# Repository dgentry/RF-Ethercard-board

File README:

This is an ENC28J60 breakout board created by maniacbug.

http://maniacbug.wordpress.com/2011/07/10/arduino-ethernet-using-enc28j60/

The latest checkin is a new layout for the board.

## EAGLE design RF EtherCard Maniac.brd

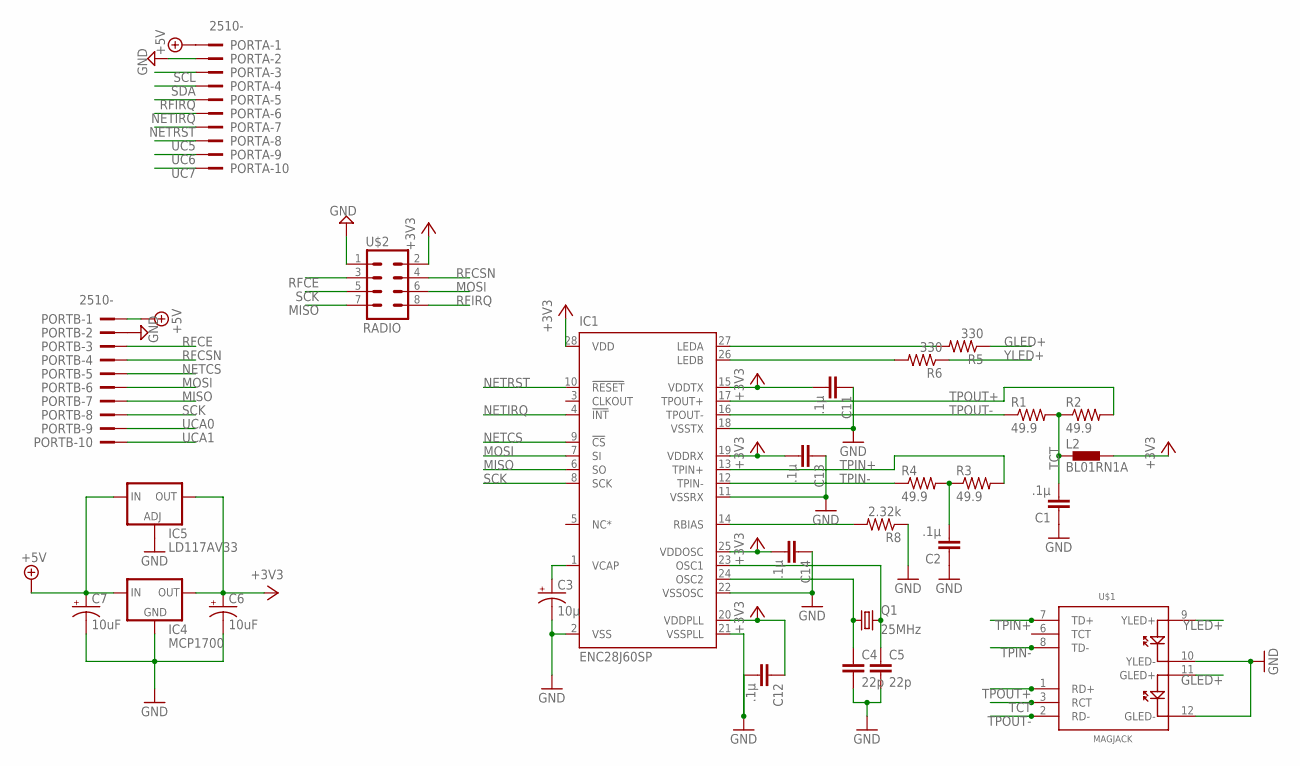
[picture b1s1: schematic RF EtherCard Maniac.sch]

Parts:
C1, C2, C11, C12, C13, C14: .1µ; CAP-PTH-SMALL
C3: 10µ; CPOL-RADIAL-10UF-25V
C4, C5: 22p; CAP-PTH-SMALL
C6, C7: 10uF; CPOL-RADIAL-10UF-25V
IC1: ENC28J60SP; DIL28-3
IC4: MCP1700; TO92A
IC5: LD117AV33; TO220L1
L2: BL01RN1A
PORTA: 2510-; PAK100/2500-10
PORTB: 2510-; PAK100/2500-10
Q1: 25MHz; HC49US
R1, R2, R3, R4: 49.9; AXIAL-0.3
R5, R6: 330; AXIAL-0.3
R8: 2.32k; AXIAL-0.3
U$1: MAGJACK
U$2: RADIO; 2X4

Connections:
+3V3: C6.1 (+), C11.2, C12.1, C13.2, C14.2, IC1.15 (VDDTX), IC1.19 (VDDRX), IC1.20 (VDDPLL), IC1.25 (VDDOSC), IC1.28 (VDD), IC4.3 (OUT), IC5.2 (OUT), L2.2, U$2.2
+5V: C7.1 (+), IC4.2 (IN), IC5.3 (IN), PORTA.1, PORTB.1
GLED+: R5.P$1 (1), U$1.11 (GLED+)
GND: C1.1, C2.1, C3.2 (-), C4.2, C5.2, C6.2 (-), C7.2 (-), C11.1, C12.2, C13.1, C14.1, IC1.2 (VSS), IC1.11 (VSSRX), IC1.18 (VSSTX), IC1.21 (VSSPLL), IC1.22 (VSSOSC), IC4.1 (GND), IC5.1 (ADJ), PORTA.2, PORTB.2, R8.P$1 (1), U$1.10 (YLED-), U$1.12 (GLED-), U$2.1
LEDA: IC1.27 (LEDA), R5.P$2 (2)
LEDB: IC1.26 (LEDB), R6.P$2 (2)
MISO: IC1.6 (SO), PORTB.7, U$2.7
MOSI: IC1.7 (SI), PORTB.6, U$2.6
unnamed: IC1.14 (RBIAS), R8.P$2 (2)
unnamed: C4.1, IC1.24 (OSC2), Q1.1
unnamed: C5.1, IC1.23 (OSC1), Q1.2
NETCS: IC1.9 (!CS), PORTB.5
NETIRQ: IC1.4 (!INT), PORTA.6
NETRST: IC1.10 (!RESET), PORTA.7
RFCE: PORTB.3, U$2.3
RFCSN: PORTB.4, U$2.4
RFIRQ: PORTA.5, U$2.8
SCK: IC1.8 (SCK), PORTB.8, U$2.5
SCL: PORTA.3
SDA: PORTA.4
TCT: C1.2, L2.1, R1.P$2 (2), R2.P$1 (1), U$1.3 (RCT)
TPGND: C2.2, R3.P$1 (1), R4.P$2 (2)
TPIN+: IC1.13 (TPIN+), R3.P$2 (2), U$1.7 (TD+)
TPIN-: IC1.12 (TPIN-), R4.P$1 (1), U$1.8 (TD-)
TPOUT+: IC1.17 (TPOUT+), R2.P$2 (2), U$1.1 (RD+)
TPOUT-: IC1.16 (TPOUT-), R1.P$1 (1), U$1.2 (RD-)
UC5: PORTA.8
UC6: PORTA.9
UC7: PORTA.10
UCA0: PORTB.9
UCA1: PORTB.10
VCAP: C3.1 (+), IC1.1 (VCAP)
YLED+: R6.P$1 (1), U$1.9 (YLED+)

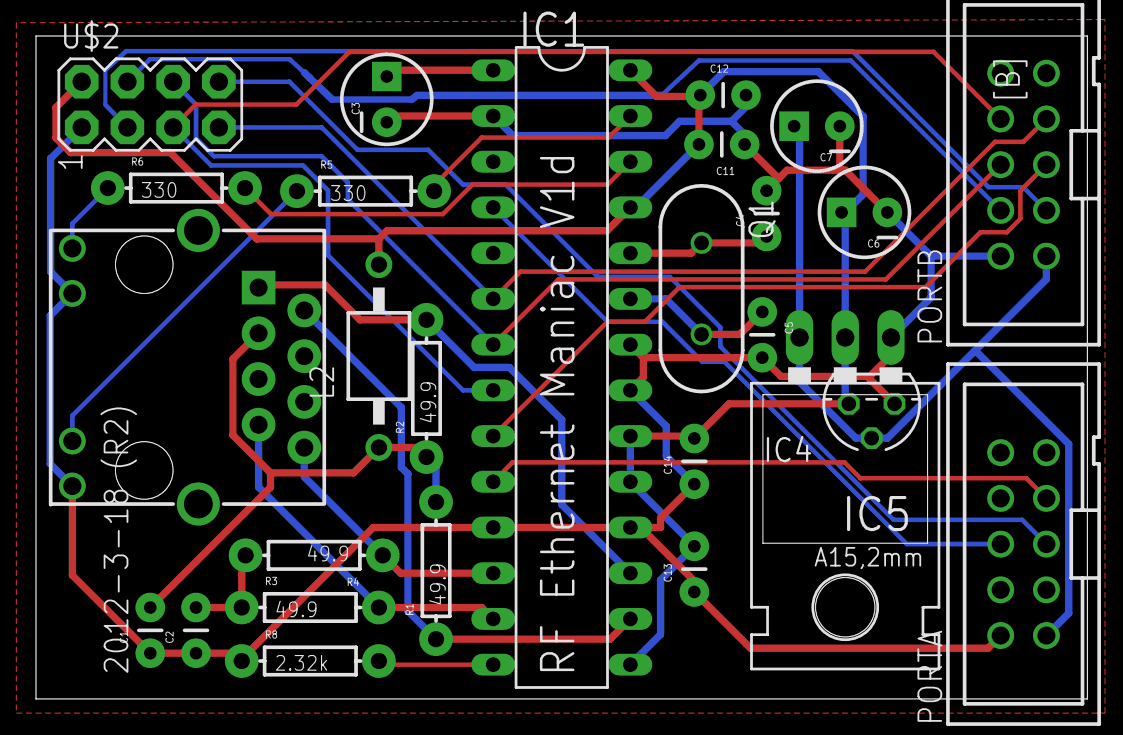
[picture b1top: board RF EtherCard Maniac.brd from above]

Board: 2 copper layers, 58.4 x 36.8 mm, 27 parts (0 on the bottom side), 26 nets.

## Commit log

2012-03-19 maniacbug's Original board and schematic
2012-03-19 Make the README point to maniacbug's blog
2012-03-19 Made traces and separations wider
2012-03-19 Smaller layout, shorter & wider traces, no vias, ground planes
2012-03-20 Matched the board colors to maniacbug's picture, and exported an image
